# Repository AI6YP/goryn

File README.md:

# Горынь

* GOWIN FPGA GW2AR-LV18QN88C8/I7 QN88
* 4 x 30pin FPC LVDS capable connectors
* FLASH 64MiB
* 3v3, 1v0 DC-DC converters

## BOM

https://ai6yp.github.io/goryn/ibom.html

## Goryn on the map

Locator: KO31ku

https://www.google.com/maps/@51.8671689,26.8422638,6338m/data=!3m1!1e3

## License

Hardware is released under the <a href="https://creativecommons.org/licenses/by/4.0/"> CC BY 4.0 </a> [[LICENSE](LICENSE)].

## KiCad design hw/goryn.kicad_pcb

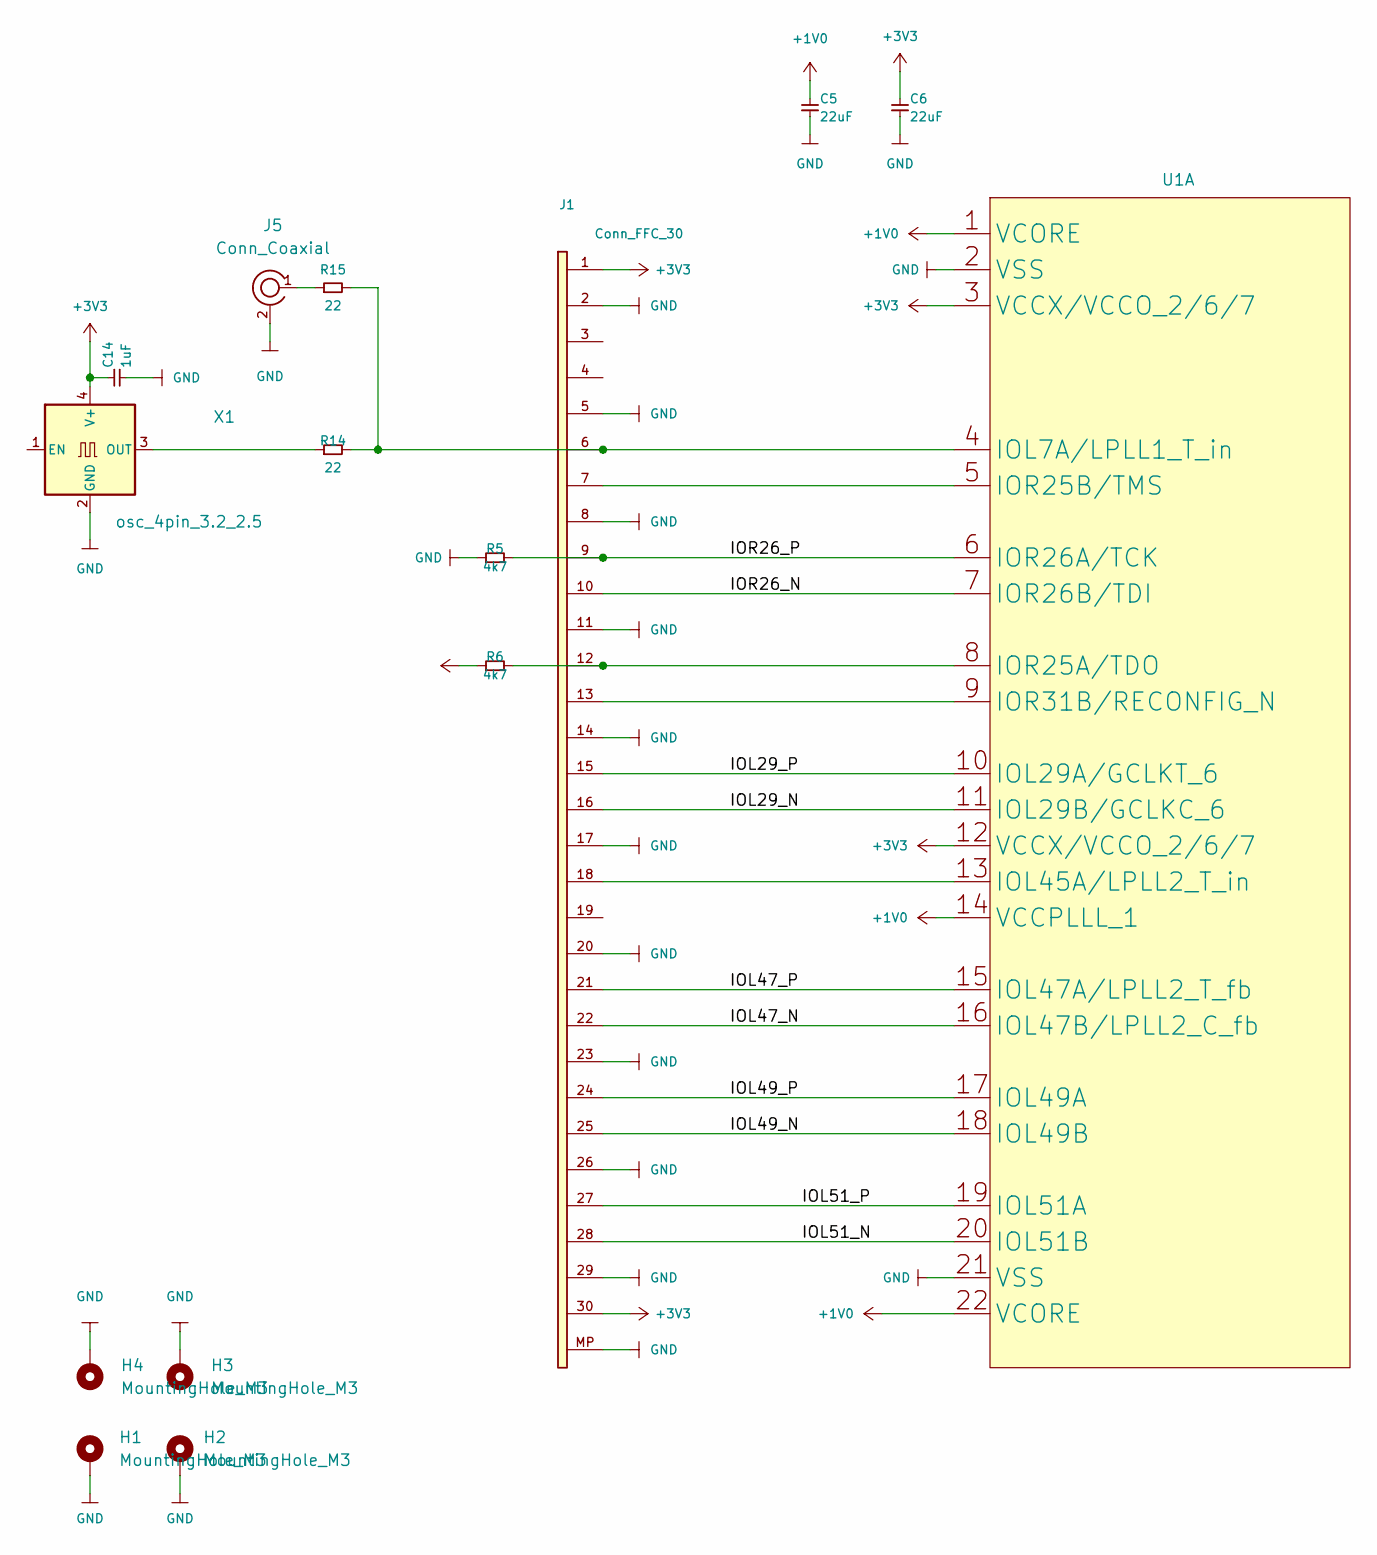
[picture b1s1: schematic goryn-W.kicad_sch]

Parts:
C5, C6: 22uF; C_0603_1608Metric
C14: 1uF; C_0603_1608Metric
H1, H2, H3, H4: MountingHole_M3; MountingHole_3.2mm_M3_Pad_Via
J1: Conn_FFC_30; Hirose_FH12-30S-0.5SH_1x30-1MP_P0.50mm_Horizontal
J5: Conn_Coaxial; U.FL_Hirose_U.FL-R-SMT-1_Vertical
R5, R6: 4k7; R_0603_1608Metric
R14, R15: 22; R_0603_1608Metric
U1: GIWIN-QFN-88-10x10mm-P0.4mm-EP6.74x6.74mm
X1: osc_4pin_3.2_2.5; Crystal_SMD_EuroQuartz_MT-4Pin_3.2x2.5mm_HandSoldering

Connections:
+1V0: C5.1, U1.1 (VCORE), U1.14 (VCCPLLL_1), U1.22 (VCORE); also elsewhere on the board
+3V3: C6.1, C14.1, J1.1, J1.30, R6.1, U1.3 (VCCX/VCCO_2/6/7), U1.12 (VCCX/VCCO_2/6/7), X1.4 (V+); also elsewhere on the board
/West/IOL29_N: J1.16, U1.11 (IOL29B/GCLKC_6)
/West/IOL29_P: J1.15, U1.10 (IOL29A/GCLKT_6)
/West/IOL47_N: J1.22, U1.16 (IOL47B/LPLL2_C_fb)
/West/IOL47_P: J1.21, U1.15 (IOL47A/LPLL2_T_fb)
/West/IOL49_N: J1.25, U1.18 (IOL49B)
/West/IOL49_P: J1.24, U1.17 (IOL49A)
/West/IOL51_N: J1.28, U1.20 (IOL51B)
/West/IOL51_P: J1.27, U1.19 (IOL51A)
/West/IOR26_N: J1.10, U1.7 (IOR26B/TDI)
/West/IOR26_P: J1.9, R5.2, U1.6 (IOR26A/TCK)
GND: C5.2, C6.2, C14.2, H1.1, H2.1, H3.1, H4.1, J1.2, J1.5, J1.8, J1.11, J1.14, J1.17, J1.20, J1.23, J1.26, J1.29, J1.MP, J5.2 (Ext), R5.1, U1.2 (VSS), U1.21 (VSS), X1.2 (GND); also elsewhere on the board
unnamed: J1.6, R14.2, R15.2, U1.4 (IOL7A/LPLL1_T_in)
unnamed: J1.7, U1.5 (IOR25B/TMS)
unnamed: J1.12, R6.2, U1.8 (IOR25A/TDO)
unnamed: J1.13, U1.9 (IOR31B/RECONFIG_N)
unnamed: J1.18, U1.13 (IOL45A/LPLL2_T_in)
unnamed: J5.1 (In), R15.1
unnamed: R14.1, X1.3 (OUT)

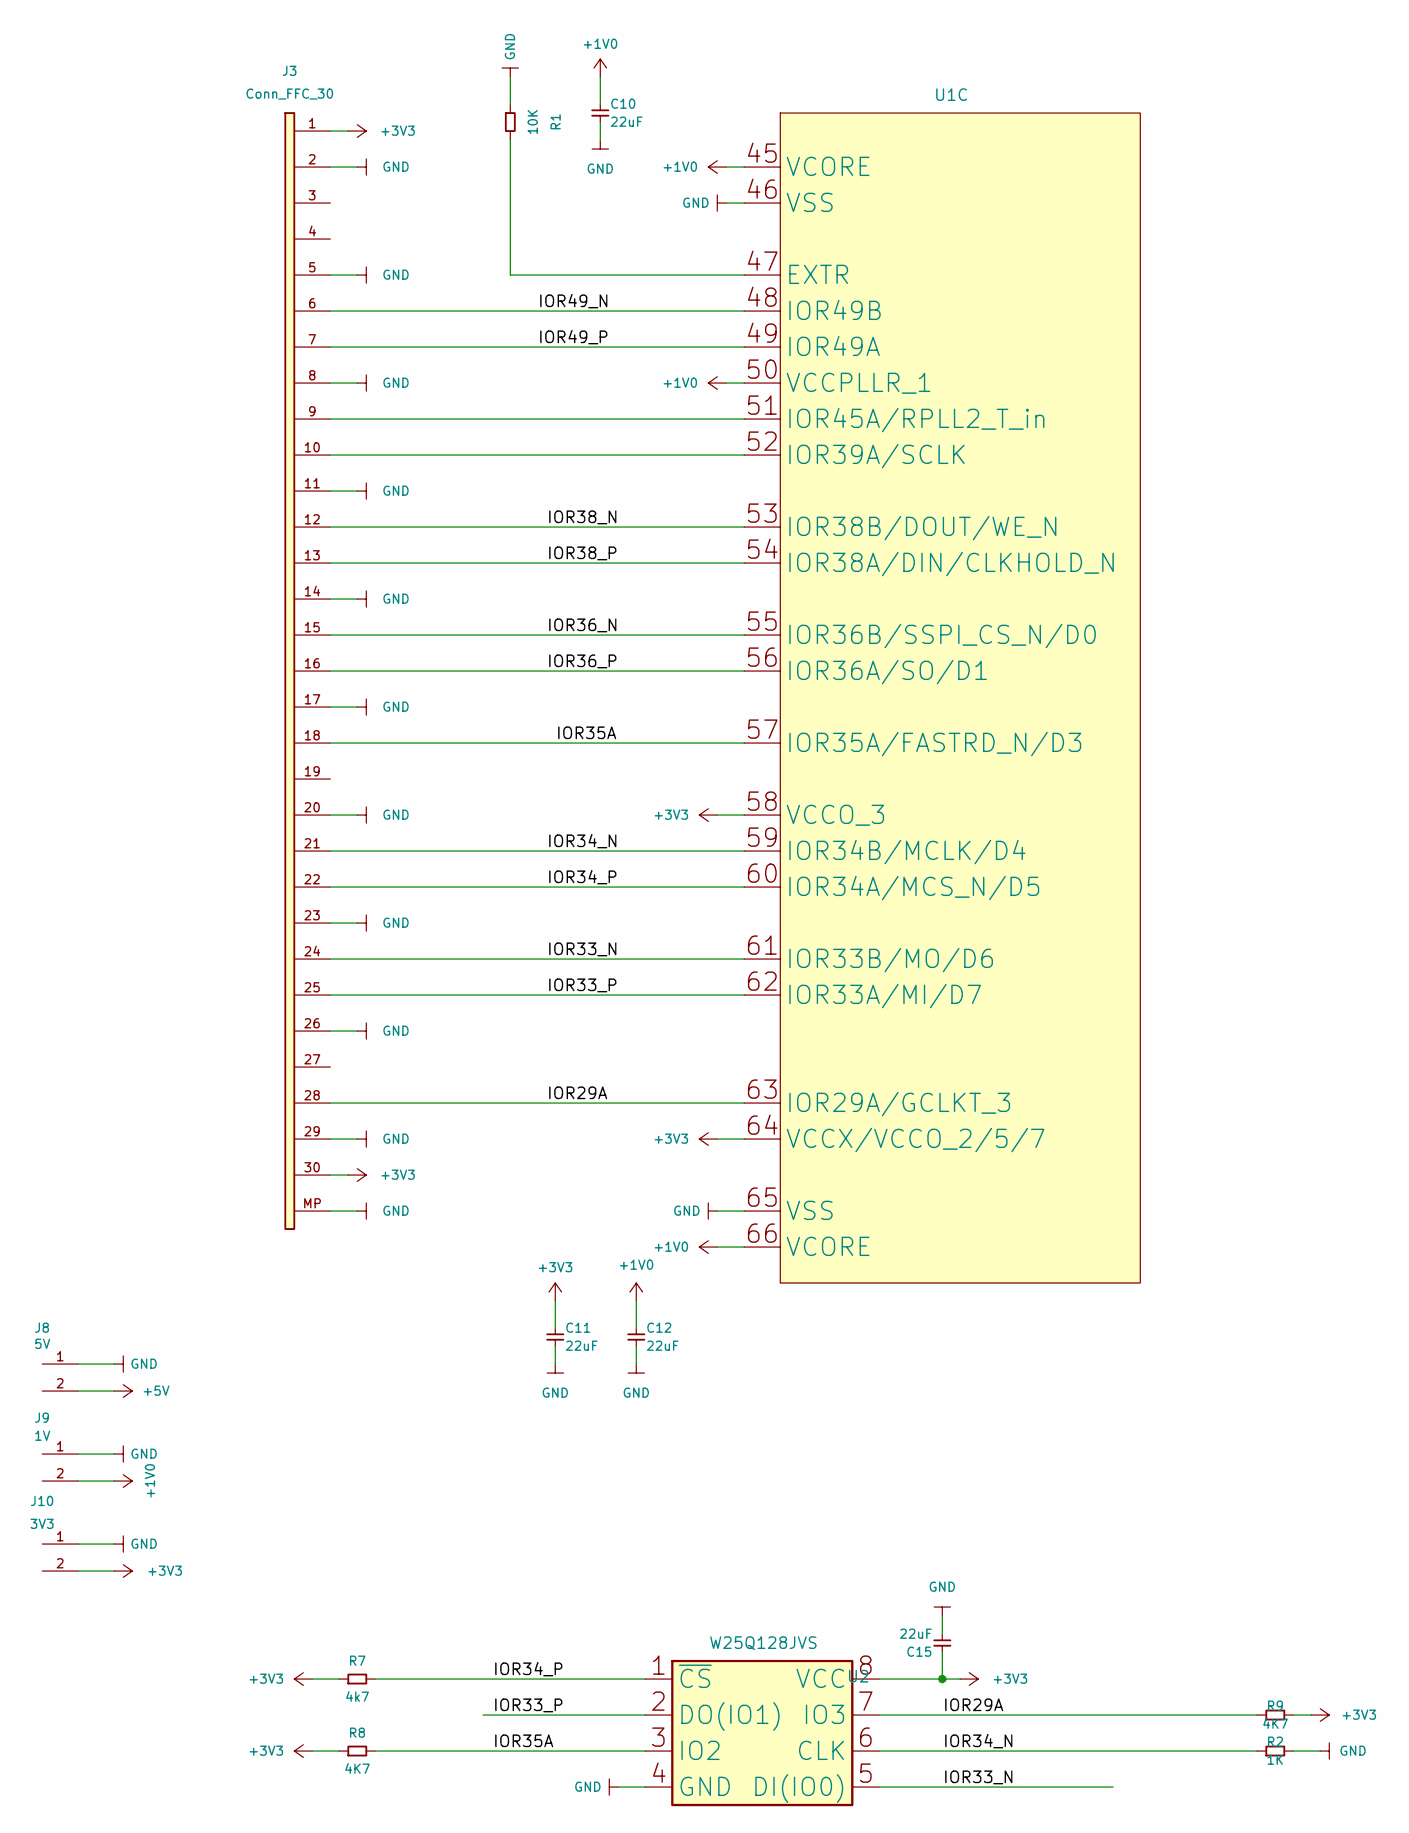
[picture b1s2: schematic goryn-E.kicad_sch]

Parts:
C10, C11, C12, C15: 22uF; C_0603_1608Metric
J3: Conn_FFC_30; Hirose_FH12-30S-0.5SH_1x30-1MP_P0.50mm_Horizontal
J8: 5V; PinHeader_1x02_P2.54mm_Vertical
J9: 1V; PinHeader_1x02_P2.54mm_Vertical
J10: 3V3; PinHeader_1x02_P2.54mm_Vertical
R1: 10K; R_0603_1608Metric
R2: 1K; R_0603_1608Metric
R7: 4k7; R_0603_1608Metric
R8, R9: 4K7; R_0603_1608Metric
U1: GIWIN-QFN-88-10x10mm-P0.4mm-EP6.74x6.74mm
U2: W25Q128JVS; SO-8_5.3x6.2mm_P1.27mm

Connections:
+1V0: C10.1, C12.1, J9.2, U1.45 (VCORE), U1.50 (VCCPLLR_1), U1.66 (VCORE); also elsewhere on the board
+3V3: C11.1, C15.1, J3.1, J3.30, J10.2, R7.1, R8.1, R9.2, U1.58 (VCCO_3), U1.64 (VCCX/VCCO_2/5/7), U2.8 (VCC); also elsewhere on the board
+5V: J8.2; also elsewhere on the board
/East/IOR29A: J3.28, R9.1, U1.63 (IOR29A/GCLKT_3), U2.7 (IO3)
/East/IOR33_N: J3.24, U1.61 (IOR33B/MO/D6), U2.5 (DI(IO0))
/East/IOR33_P: J3.25, U1.62 (IOR33A/MI/D7), U2.2 (DO(IO1))
/East/IOR34_N: J3.21, R2.1, U1.59 (IOR34B/MCLK/D4), U2.6 (CLK)
/East/IOR34_P: J3.22, R7.2, U1.60 (IOR34A/MCS_N/D5), U2.1 (~CS)
/East/IOR35A: J3.18, R8.2, U1.57 (IOR35A/FASTRD_N/D3), U2.3 (IO2)
/East/IOR36_N: J3.15, U1.55 (IOR36B/SSPI_CS_N/D0)
/East/IOR36_P: J3.16, U1.56 (IOR36A/SO/D1)
/East/IOR38_N: J3.12, U1.53 (IOR38B/DOUT/WE_N)
/East/IOR38_P: J3.13, U1.54 (IOR38A/DIN/CLKHOLD_N)
/East/IOR49_N: J3.6, U1.48 (IOR49B)
/East/IOR49_P: J3.7, U1.49 (IOR49A)
GND: C10.2, C11.2, C12.2, C15.2, J3.2, J3.5, J3.8, J3.11, J3.14, J3.17, J3.20, J3.23, J3.26, J3.29, J3.MP, J8.1, J9.1, J10.1, R1.1, R2.2, U1.46 (VSS), U1.65 (VSS), U2.4 (GND); also elsewhere on the board
unnamed: J3.9, U1.51 (IOR45A/RPLL2_T_in)
unnamed: J3.10, U1.52 (IOR39A/SCLK)
unnamed: R1.2, U1.47 (EXTR)

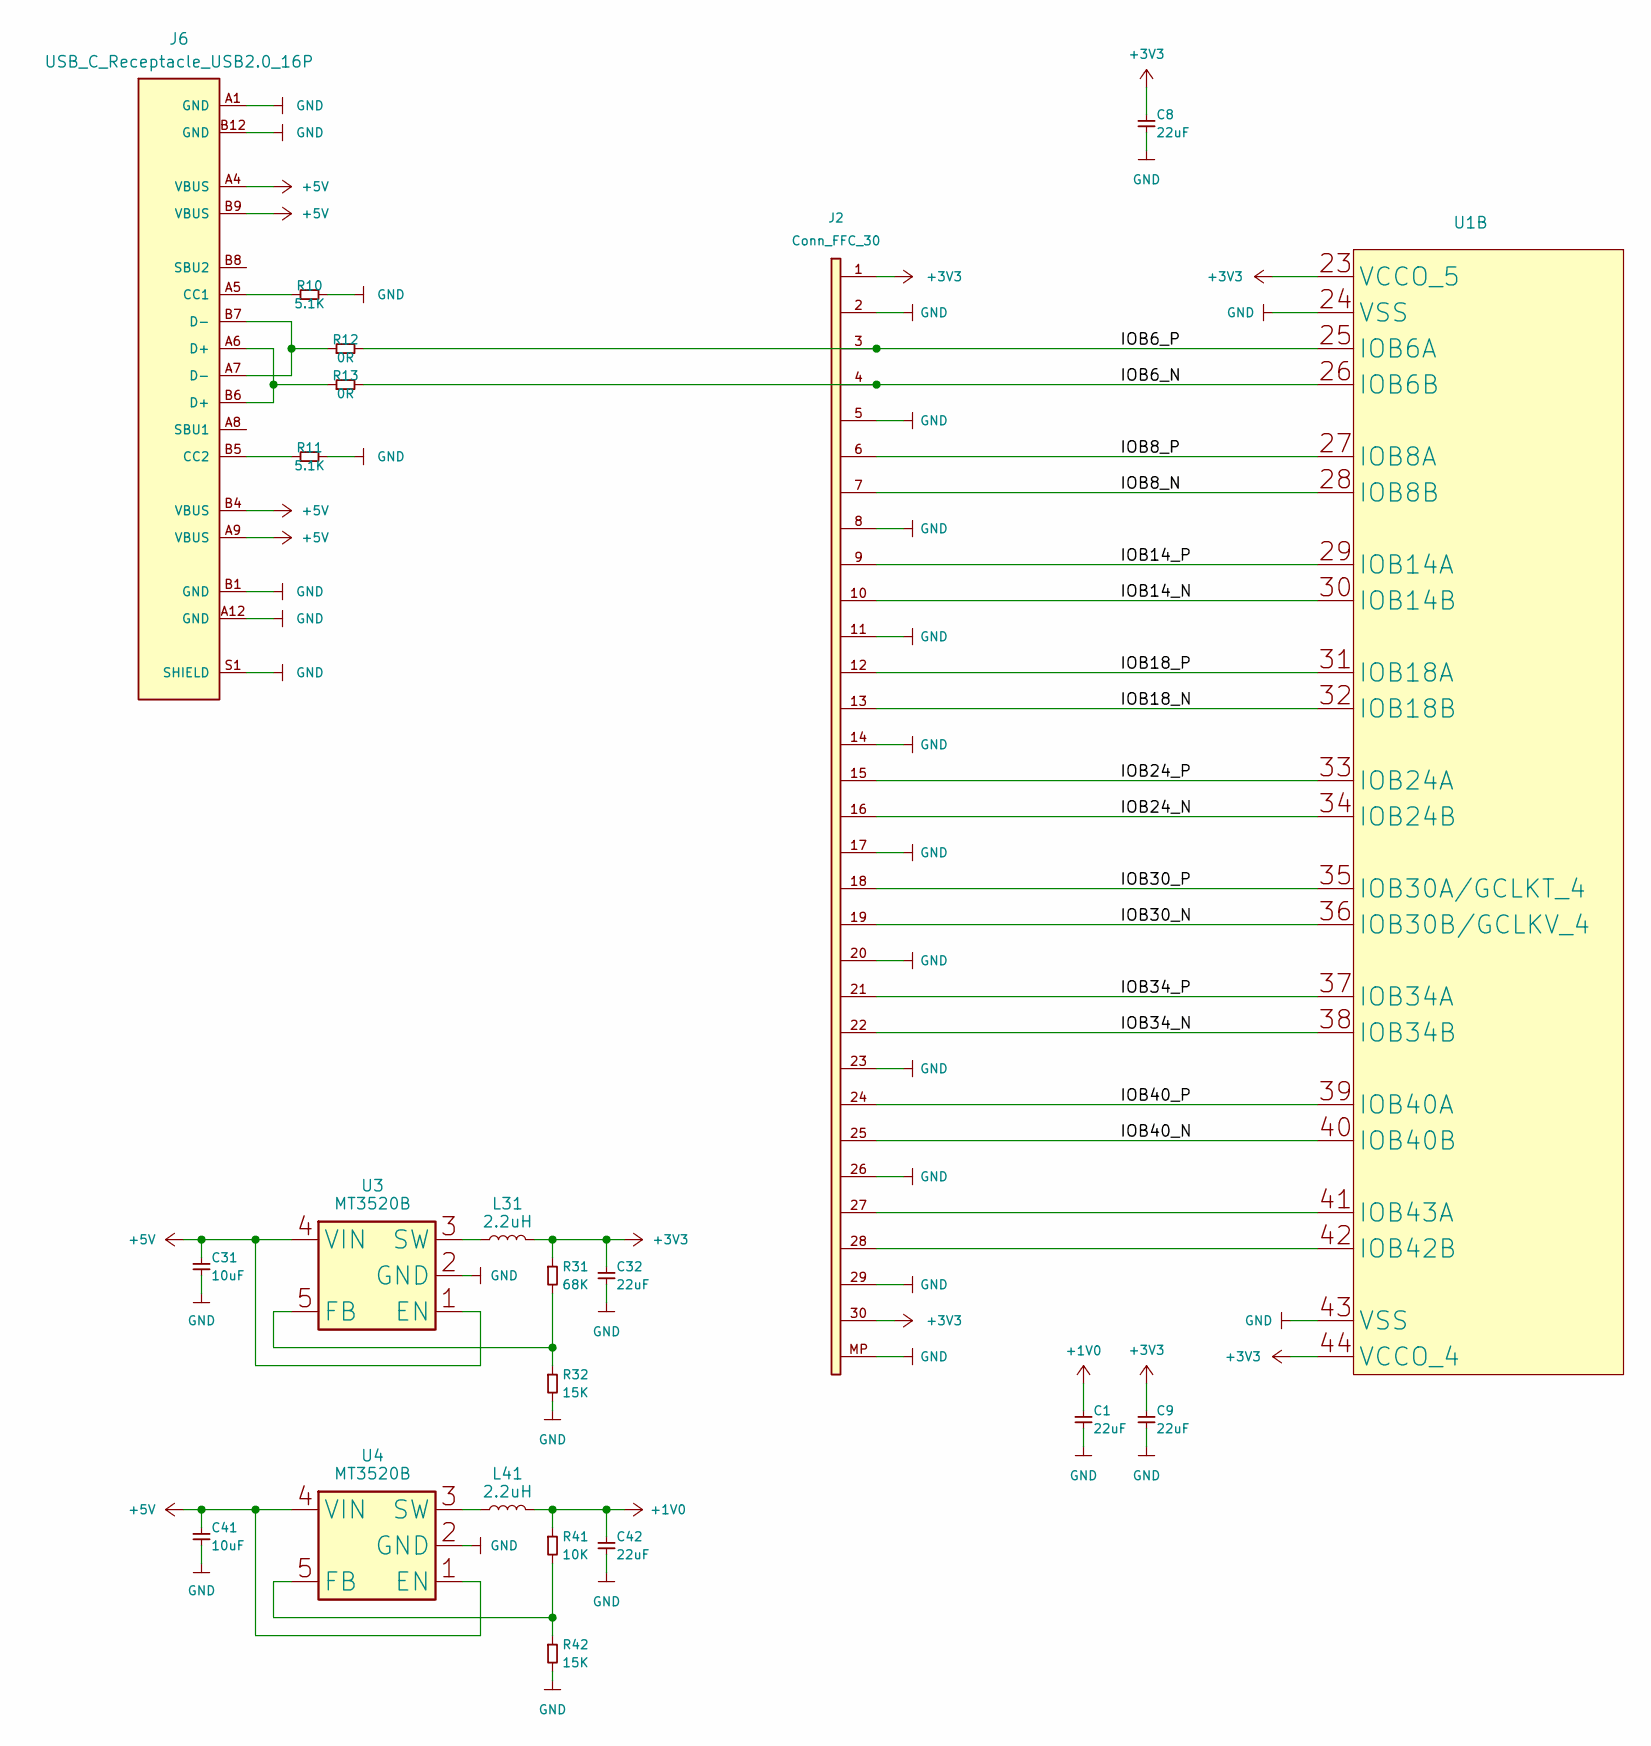
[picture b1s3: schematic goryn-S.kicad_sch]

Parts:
C1, C8, C9, C32, C42: 22uF; C_0603_1608Metric
C31, C41: 10uF; C_0603_1608Metric
J2: Conn_FFC_30; Hirose_FH12-30S-0.5SH_1x30-1MP_P0.50mm_Horizontal
J6: USB_C_Receptacle_USB2.0_16P; USB_C_Receptacle_GCT_USB4105-xx-A_16P_TopMnt_Horizontal
L31, L41: 2.2uH; L_0805_2012Metric_Pad1.05x1.20mm_HandSolder
R10, R11: 5.1K; R_0603_1608Metric
R12, R13: 0R; R_0603_1608Metric
R31: 68K; R_0603_1608Metric
R32, R42: 15K; R_0603_1608Metric
R41: 10K; R_0603_1608Metric
U1: GIWIN-QFN-88-10x10mm-P0.4mm-EP6.74x6.74mm
U3, U4: MT3520B; SOT-23-5

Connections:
+1V0: C1.1, C42.1, L41.2, R41.1; also elsewhere on the board
+3V3: C8.1, C9.1, C32.1, J2.1, J2.30, L31.2, R31.1, U1.23 (VCCO_5), U1.44 (VCCO_4); also elsewhere on the board
+5V: C31.1, C41.1, J6.A4 (VBUS), J6.A9 (VBUS), J6.B4 (VBUS), J6.B9 (VBUS), U3.1 (EN), U3.4 (VIN), U4.1 (EN), U4.4 (VIN); also elsewhere on the board
/South/IOB6_N: J2.4, R13.2, U1.26 (IOB6B)
/South/IOB6_P: J2.3, R12.2, U1.25 (IOB6A)
/South/IOB8_N: J2.7, U1.28 (IOB8B)
/South/IOB8_P: J2.6, U1.27 (IOB8A)
/South/IOB14_N: J2.10, U1.30 (IOB14B)
/South/IOB14_P: J2.9, U1.29 (IOB14A)
/South/IOB18_N: J2.13, U1.32 (IOB18B)
/South/IOB18_P: J2.12, U1.31 (IOB18A)
/South/IOB24_N: J2.16, U1.34 (IOB24B)
/South/IOB24_P: J2.15, U1.33 (IOB24A)
/South/IOB30_N: J2.19, U1.36 (IOB30B/GCLKV_4)
/South/IOB30_P: J2.18, U1.35 (IOB30A/GCLKT_4)
/South/IOB34_N: J2.22, U1.38 (IOB34B)
/South/IOB34_P: J2.21, U1.37 (IOB34A)
/South/IOB40_N: J2.25, U1.40 (IOB40B)
/South/IOB40_P: J2.24, U1.39 (IOB40A)
GND: C1.2, C8.2, C9.2, C31.2, C32.2, C41.2, C42.2, J2.2, J2.5, J2.8, J2.11, J2.14, J2.17, J2.20, J2.23, J2.26, J2.29, J2.MP, J6.A1 (GND), J6.A12 (GND), J6.B1 (GND), J6.B12 (GND), J6.S1 (SHIELD), R10.2, R11.2, R32.2, R42.2, U1.24 (VSS), U1.43 (VSS), U3.2 (GND), U4.2 (GND); also elsewhere on the board
unnamed: J2.27, U1.41 (IOB43A)
unnamed: J2.28, U1.42 (IOB42B)
unnamed: J6.A5 (CC1), R10.1
unnamed: J6.B5 (CC2), R11.1
unnamed: J6.A6 (D+), J6.B6 (D+), R13.1
unnamed: J6.A7 (D-), J6.B7 (D-), R12.1
unnamed: R31.2, R32.1, U3.5 (FB)
unnamed: L31.1, U3.3 (SW)
unnamed: R41.2, R42.1, U4.5 (FB)
unnamed: L41.1, U4.3 (SW)

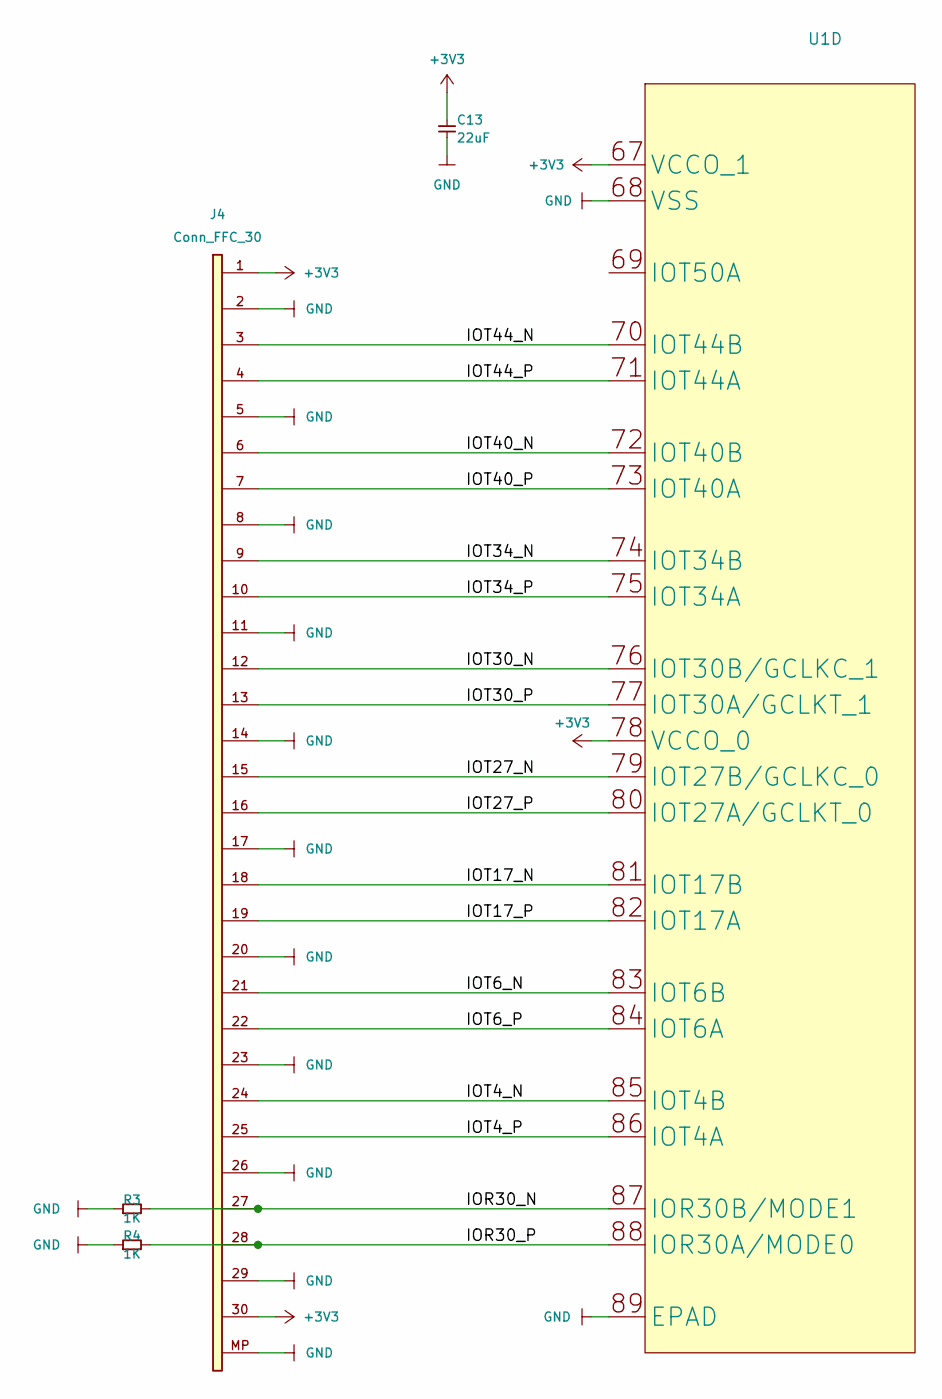
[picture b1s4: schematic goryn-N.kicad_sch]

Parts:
C13: 22uF; C_0603_1608Metric
J4: Conn_FFC_30; Hirose_FH12-30S-0.5SH_1x30-1MP_P0.50mm_Horizontal
R3, R4: 1K; R_0603_1608Metric
U1: GIWIN-QFN-88-10x10mm-P0.4mm-EP6.74x6.74mm

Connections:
+3V3: C13.1, J4.1, J4.30, U1.67 (VCCO_1), U1.78 (VCCO_0); also elsewhere on the board
/North/IOR30_N: J4.27, R3.2, U1.87 (IOR30B/MODE1)
/North/IOR30_P: J4.28, R4.2, U1.88 (IOR30A/MODE0)
/North/IOT4_N: J4.24, U1.85 (IOT4B)
/North/IOT4_P: J4.25, U1.86 (IOT4A)
/North/IOT6_N: J4.21, U1.83 (IOT6B)
/North/IOT6_P: J4.22, U1.84 (IOT6A)
/North/IOT17_N: J4.18, U1.81 (IOT17B)
/North/IOT17_P: J4.19, U1.82 (IOT17A)
/North/IOT27_N: J4.15, U1.79 (IOT27B/GCLKC_0)
/North/IOT27_P: J4.16, U1.80 (IOT27A/GCLKT_0)
/North/IOT30_N: J4.12, U1.76 (IOT30B/GCLKC_1)
/North/IOT30_P: J4.13, U1.77 (IOT30A/GCLKT_1)
/North/IOT34_N: J4.9, U1.74 (IOT34B)
/North/IOT34_P: J4.10, U1.75 (IOT34A)
/North/IOT40_N: J4.6, U1.72 (IOT40B)
/North/IOT40_P: J4.7, U1.73 (IOT40A)
/North/IOT44_N: J4.3, U1.70 (IOT44B)
/North/IOT44_P: J4.4, U1.71 (IOT44A)
GND: C13.2, J4.2, J4.5, J4.8, J4.11, J4.14, J4.17, J4.20, J4.23, J4.26, J4.29, J4.MP, R3.1, R4.1, U1.68 (VSS), U1.89 (EPAD); also elsewhere on the board

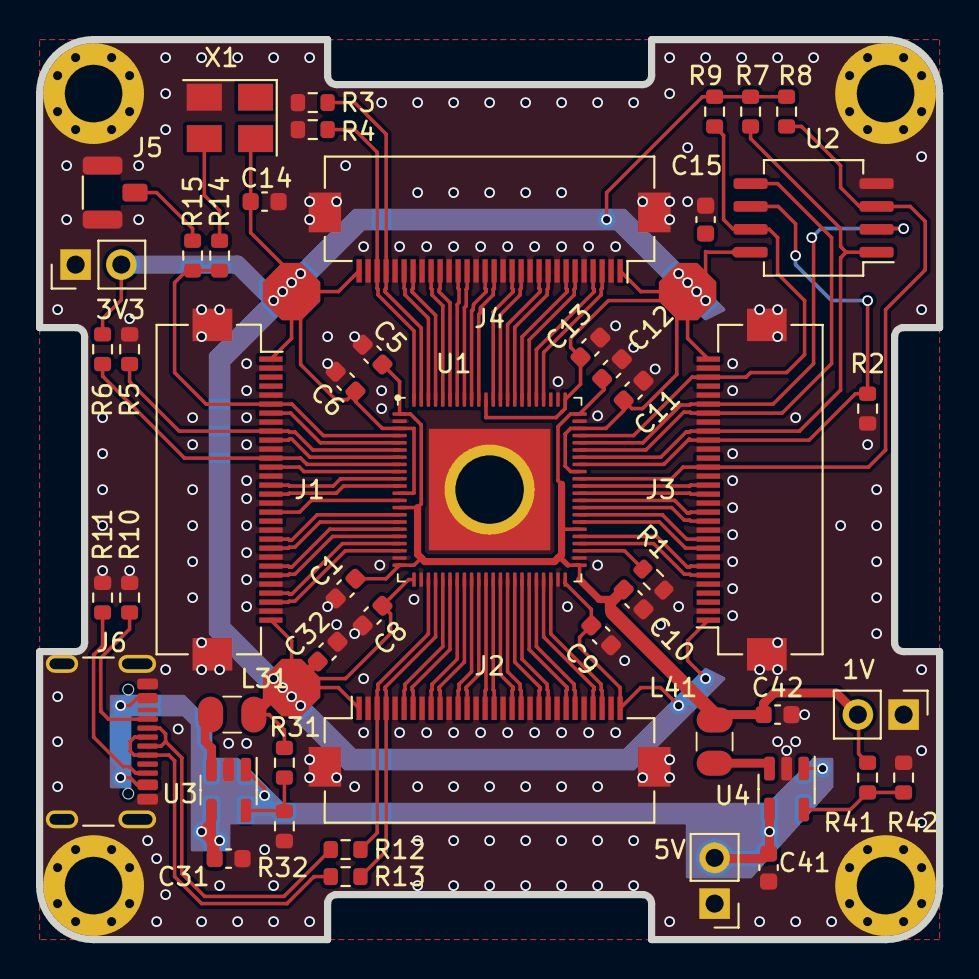
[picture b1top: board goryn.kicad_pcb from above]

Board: 2 copper layers, 50.0 x 50.0 mm, 54 parts (0 on the bottom side), 80 nets.

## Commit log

2024-02-24 initial kicad fiels
2024-02-24 added DC-DC
2024-02-25 FFC34 -> FFC30
2024-02-28 on the map
2024-02-29 connectors spreadsheet
2024-02-29 happy kicad 8
2024-03-01 Create LICENSE
2024-03-01 CC license added
2024-03-11 finished routing
2024-03-12 added interactive BOM
2024-03-12 added link to BOM
2024-03-18 v1.0.0
2024-03-18 Added Locator
2024-03-18 updated BOM
